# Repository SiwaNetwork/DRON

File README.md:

# 🚁 Final Drone Swarm Simulation

**Ультра-реалистичная симуляция роя дронов с многоуровневыми эшелонами, продвинутыми алгоритмами синхронизации и физически точными моделями связи**

## 🌟 Основные возможности

### ✈️ Многоуровневые эшелоны полета
- **5 эшелонов высоты** (60м - 140м)
- **Умное распределение дронов** по ролям
- **ПИД-регулятор высоты** для стабилизации
- **Автоматическое поддержание формации**

### 🔄 Продвинутая синхронизация
- **IEEE 1588 PTP** - точность до 10-100 наносекунд
- **NTP-подобные алгоритмы** для сетевой синхронизации
- **Консенсус-алгоритмы** для распределенной синхронизации
- **Адаптивная синхронизация** с компенсацией задержек

### 🕐 Различные типы генераторов тактовых импульсов
- **Мастер-дроны**: Rubidium, Cesium, GPS-Disciplined OCXO, Hydrogen Maser
- **Ведомые дроны**: OCXO, TCXO, Quartz, Crystal
- **Реалистичные характеристики** дрейфа и стабильности

### 🛡️ Система отказоустойчивости
- **Автоматическое переключение мастер-дрона**
- **Алгоритмы выборов лидера** (Priority, RAFT, Byzantine Fault Tolerant)
- **Обнаружение потери связи**
- **Восстановление синхронизации**

### 📡 Физически точные модели связи
- **Частотные диапазоны**: 433MHz, 900MHz, 1.2GHz, 2.4GHz, 5GHz, 5.8GHz
- **Ширина каналов**: 20/40/80/160 MHz
- **Модели помех**: Rural, Suburban, Urban, Indoor, Industrial
- **Уравнение Фрииса** для расчета затухания сигнала
- **Эффект Доплера** для движущихся дронов
- **Многолучевое распространение**
- **Атмосферное поглощение**

### 🎮 Интерактивная 3D визуализация
- **Three.js** для реалистичной графики
- **Реалистичные модели дронов** с вращающимися пропеллерами
- **Визуализация синхронизации** с цветными линиями
- **Реалистичная местность** с дорогами, зданиями, деревьями
- **Динамическое освещение** и туман

## 🚀 Быстрый старт

### Требования
- Python 3.7+
- Веб-браузер с поддержкой WebGL

### Установка и запуск
```bash
# Клонирование репозитория
git clone https://github.com/your-username/drone-swarm-simulation.git
cd drone-swarm-simulation

# Запуск симуляции
python final_drone_simulation.py
```

### Открытие в браузере
Автоматически откроется браузер по адресу: `http://localhost:8080`

## 🎯 Управление симуляцией

### Основные элементы интерфейса
1. **Панель конфигурации** (слева)
   - Параметры роя
   - Настройки синхронизации
   - Конфигурация отказоустойчивости
   - Радиочастотные параметры

2. **3D сцена** (центр)
   - Интерактивная камера (мышь)
   - Визуализация дронов и их движения
   - Линии синхронизации

3. **Панель метрик** (справа)
   - Время симуляции
   - Качество синхронизации
   - Статус DPLL
   - Информация об эшелонах

### Кнопки управления
- **Запустить симуляцию** - начало работы роя
- **Остановить симуляцию** - остановка всех процессов
- **Обновить конфигурацию** - применение новых параметров

## ⚙️ Конфигурация

### Параметры роя
- **Количество дронов**: 5-50
- **Радиус роя**: 100-2000 метров
- **Высота полета**: 50-300 метров

### Алгоритмы синхронизации
- **Master-Slave**: Классическая топология
- **Peer-to-Peer**: Равноправная синхронизация
- **Hierarchical**: Иерархическая структура
- **Mesh**: Сетевая топология

### Частотные диапазоны
- **433MHz**: Дальняя связь, низкая скорость
- **900MHz**: Средняя дальность
- **1.2GHz**: Авиационные частоты
- **2.4GHz**: WiFi диапазон
- **5GHz**: Высокоскоростная связь
- **5.8GHz**: FPV и управление

## 🔬 Технические детали

### Архитектура системы
```
┌─────────────────┐    ┌─────────────────┐    ┌─────────────────┐
│   Web Frontend  │    │  Python Backend │    │  Simulation     │
│   (Three.js)    │◄──►│  (HTTP Server)  │◄──►│  Engine         │
│                 │    │                 │    │                 │
│ - 3D Rendering  │    │ - API Endpoints │    │ - Drone Physics │
│ - UI Controls   │    │ - State Mgmt    │    │ - Sync Logic    │
│ - Real-time     │    │ - Threading     │    │ - Failover      │
└─────────────────┘    └─────────────────┘    └─────────────────┘
```

### Алгоритмы синхронизации

#### IEEE 1588 PTP (Precision Time Protocol)
```python
# Обмен сообщениями для точной синхронизации
Sync: Master → Slave (T1)
Follow_Up: Master → Slave (T1 точное время)
Delay_Req: Slave → Master (T2)
Delay_Resp: Master → Slave (T3)

# Расчет задержки и смещения
delay = ((T2 - T1) + (T4 - T3)) / 2
offset = ((T2 - T1) - (T4 - T3)) / 2
```

#### Консенсус-алгоритмы
- **RAFT**: Выбор лидера с логическими часами
- **Byzantine Fault Tolerant**: Защита от византийских ошибок
- **Priority-based**: Выбор по приоритету (тип часов, стабильность)

### Физические модели

#### Уравнение Фрииса
```
L = 20 * log10(f) + 20 * log10(d) + 20 * log10(4π/c) + L_extra
```
где:
- `f` - частота (Гц)
- `d` - расстояние (м)
- `c` - скорость света
- `L_extra` - дополнительные потери

#### Эффект Доплера
```
f_shift = f * (v * cos(θ)) / c
```
где:
- `f` - исходная частота
- `v` - относительная скорость
- `θ` - угол между векторами скорости и направления сигнала

## 📊 Метрики и мониторинг

### Качество синхронизации
- **Время смещения**: Разность времени между дронами
- **Джиттер**: Вариации задержки
- **Точность**: Стандартное отклонение ошибки
- **Стабильность**: Долгосрочная стабильность частоты

### Физические параметры
- **SNR**: Отношение сигнал/шум
- **Затухание сигнала**: Потери в канале связи
- **Многолучевые задержки**: Задержки от отражений
- **Доплеровский сдвиг**: Сдвиг частоты от движения

### Статус системы
- **Активный мастер**: Текущий ведущий дрон
- **Смены мастера**: Количество переключений
- **Активные выборы**: Текущие процессы выборов
- **Эшелоны**: Распределение по высотам

## 🎨 Визуализация

### Цветовая схема дронов
- **Красный**: Rubidium генераторы (мастер)
- **Зеленый**: OCXO генераторы
- **Синий**: TCXO генераторы
- **Желтый**: Quartz генераторы
- **Яркость**: Зависит от эшелона (темнее = ниже)

### Анимации
- **Вращение пропеллеров**: Реалистичное движение
- **Пульсация маяка**: Индикация мастер-дрона
- **Кольца синхронизации**: Визуализация качества связи
- **Линии связи**: Цветные линии между дронами

## 🔧 Расширение функциональности

### Добавление новых алгоритмов
```python
class CustomSyncAlgorithm:
    def __init__(self):
        self.name = "Custom Algorithm"
    
    def synchronize(self, drone, neighbors):
        # Ваша логика синхронизации
        pass
```

### Новые типы генераторов
```python
class CustomClock:
    def __init__(self):
        self.drift_rate = 1e-9  # дрейф в секундах/секунду
        self.stability = 1e-12  # стабильность Аллана
        self.accuracy = 1e-6    # точность в секундах
```

### Дополнительные модели помех
```python
def custom_interference_model(frequency, distance, environment):
    # Ваша модель помех
    return interference_level
```

## 📝 Лицензия

MIT License - см. файл [LICENSE](LICENSE)

## 🤝 Вклад в проект

1. Форкните репозиторий
2. Создайте ветку для новой функции
3. Внесите изменения
4. Создайте Pull Request

## 📞 Поддержка

- **Issues**: [GitHub Issues](https://github.com/your-username/drone-swarm-simulation/issues)
- **Discussions**: [GitHub Discussions](https://github.com/your-username/drone-swarm-simulation/discussions)
- **Email**: your-email@example.com

## 🙏 Благодарности

- **Three.js** - 3D графика
- **IEEE 1588** - стандарт точной синхронизации
- **DJI** - вдохновение для реалистичных параметров дронов

---

**Версия**: 2.0.0  
**Последнее обновление**: Август 2025  
**Автор**: Your Name

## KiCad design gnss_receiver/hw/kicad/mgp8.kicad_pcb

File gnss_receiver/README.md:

# МГП-8 — многосистемный многочастотный приёмник ГНСС (ШИВА.468157.001)

Открытая разработка модуля приёмника ГЛОНАСС/GPS/Galileo/BeiDou/QZSS/NavIC/SBAS.
В проект входят схема, конфигурация ПЛИС, программное обеспечение МК, моделирование
и конструкторская документация по ЕСКД.

Архитектура:

- 8 ВЧ-трактов MAX2771 (по схеме Pocket SDR FE 8CH), 2-битные I/Q, 24 МГц;
- ПЛИС LFE5U-45F (коррелятор на 80 каналов, режекторный фильтр, шкала времени, 1PPS);
- МК STM32H743 (захват, слежение, навигация, протоколы, шина FMC к ПЛИС);
- контроллер USB 3.0 FX3 для выдачи «сырых» отсчётов в формате Pocket SDR.

## Состав

| Каталог | Содержание |
|---|---|
| `docs/` | исходные тексты документов: обзор открытых разработок, ТЗ, ПЗ, ПМ, описание программы |
| `kd/` | КД в PDF (подлинник): Э1, Э3, ПЭ3, спецификация, ВП, ТЗ, ПЗ, ПМ, описание программы ПО МК; текстовые документы и перечни — также в DOCX (редактируемая копия для Word) |
| `hw/gen/` | схема Э3 «как код» (Python) → проект KiCad 7/10 (`hw/kicad/`), перечни ЕСКД |
| `hw/spice/` | SPICE-модели узлов: питание антенны, bias-tee, вход REF, выход 1PPS |
| `fpga/rtl/` | Verilog: `corr_engine` (16 каналов на движок), `corr_bank`, `notch`, `rf_capture`, `timebase`, `fmc_slave`, `max_spi`, `snapshot`, `acq_fft` (ускоритель захвата), `mgp8_core`, `mgp8_top` |
| `fpga/model/` | битово-точные модели коррелятора, режекторного фильтра и ускорителя захвата (Python) |
| `fpga/tb/` | тесты RTL: сверка с моделями, системный тест через шину FMC |
| `sw/fw/` | ПО МК (C99): драйвер коррелятора, захват (в т. ч. слабых сигналов), слежение (ФАП 3-го порядка, длительное накопление, повторный захват), GPS LNAV, строки ГЛОНАСС, Galileo I/NAV, BeiDou D1, эфемериды, PVT (GPS, ГЛОНАСС, Galileo, BeiDou), 1PPS, NMEA, RTCM 3.3, собственный двоичный протокол, спектральный контроль; тесты на ПК |
| `sw/pyrx/` | эталонный программный приёмник и имитатор сигналов (Python) |
| `sim/` | расчёты: частотный план, энергетика ВЧ-тракта, сигналы, PVT/DOP, режекторный фильтр, мощность и тепловой режим, надёжность |
| `tools/` | оформление PDF и DOCX по ЕСКД (рамки, штампы), шрифт osifont с исправлениями |

## Инструменты

Используются: Python 3 (numpy, scipy, matplotlib, reportlab, python-docx), Icarus Verilog,
Yosys, nextpnr-ecp5 и Project Trellis (ecppack), ngspice, gcc и KiCad 7 или 10 (kicad-cli).
Для `tests/check_output.py` нужны также pyrtcm и pynmeagps.

## Проверка

```sh
# ПЛИС: движок коррелятора, режекторный фильтр, система целиком (сверка с моделями)
make -C fpga sim
# ПЛИС: синтез, размещение и трассировка, файл конфигурации build/mgp8.bit
# (100,15 МГц при требуемых 96 МГц; готовый файл — fpga/bit/mgp8.bit)
make -C fpga syn
# ПО МК: модульные тесты (коды, модель ПЛИС, LNAV, строки ГЛОНАСС, I/NAV, D1, решение, протоколы,
# спектр и режекторный фильтр, захват слабых сигналов) и сквозной «ПЧ → слежение» (L1 C/A)
make -C sw/fw test
# ПО МК: длительные тесты (≈ 70 мин): динамика 4g, слабые сигналы и повторный захват,
# сквозные «ПЧ → координаты, 1PPS» по GPS, по GPS + ГЛОНАСС, двухчастотный GPS L1 + L2C,
# GPS + Galileo + BeiDou и двухчастотные пары L1 + L5, G1 + G2, E1 + E5a, B1I + B3I
make -C sw/fw test-long
# расчёты (результаты — sim/out/*.md, *.png)
python3 sim/rf_budget.py; python3 sim/freq_plan.py; python3 sim/notch_sim.py
python3 sim/power_budget.py; python3 sim/reliability.py
# схема и перечни (Э3, ПЭ3, спецификация, ВП); текстовые документы (ТЗ, ПЗ, ПМ, описание программы).
# Перечни и текстовые документы выходят в PDF и DOCX; правки вносятся в исходники (docs/*.md,
# hw/gen), DOCX пересобирается вместе с PDF
python3 hw/gen/build.py --pdf
python3 hw/gen/eskd_lists.py
python3 tools/build_docs.py
# вычислительное ядро ПО МК для STM32H743 (arm-none-eabi-gcc)
make -C sw/fw mcu
```

## Цепочка верификации

Каждый вычислительный блок ПЛИС описан дважды: битово-точной моделью на Python
и моделью на C (`sw/fw/src/corr_sim.c`), на которой работает ПО МК в тестах.
Результаты RTL сверяются с моделью отсчёт в отсчёт. Тесты ПО МК используют ту же
модель ПЛИС, поэтому сквозная проверка «ПЧ → координаты» проходит через реальные
регистры и протокол обмена ПЛИС–МК.

Выходные протоколы NMEA и RTCM дополнительно проверяются независимыми декодерами
(pynmeagps, pyrtcm).

## Копия на ПК

Рабочую копию репозитория в папке «Документы», обновляемую из GitHub по расписанию, ведут
скрипты `tools/sync/sync_documents.ps1` (Windows) и `tools/sync/sync_documents.sh`
(Linux, macOS). Установка — в `tools/sync/README.md`.

## Состояние

Результаты расчётов, моделирования и проверок, а также соответствие ТЗ сведены
в пояснительной записке (`docs/03_ПЗ.md`, `kd/ШИВА.468157.001 ПЗ.pdf`). Там же,
в разделе 9, перечислены нерешённые вопросы. Основные из них:

- разводка печатной платы;
- платформенная часть ПО МК;
- навигационное сообщение BeiDou D2 (КА GEO), пара BeiDou B1I + B2a (нужно сообщение B-CNAV);
- изготовление и испытания опытного образца.

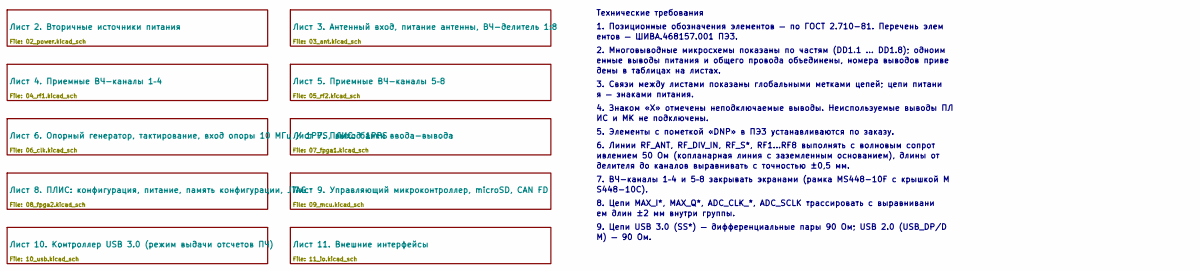
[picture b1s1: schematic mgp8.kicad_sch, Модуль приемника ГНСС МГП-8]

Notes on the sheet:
Технические требования
1. Позиционные обозначения элементов — по ГОСТ 2.710-81. Перечень элем
ентов — ШИВА.468157.001 ПЭ3.
2. Многовыводные микросхемы показаны по частям (DD1.1 … DD1.8); одноим
енные выводы питания и общего провода объединены, номера выводов приве
дены в таблицах на листах.
3. Связи между листами показаны глобальными метками цепей; цепи питани
я — знаками питания.
4. Знаком «X» отмечены неподключаемые выводы. Неиспользуемые выводы ПЛ
ИС и МК не подключены.
5. Элементы с пометкой «DNP» в ПЭ3 устанавливаются по заказу.
6. Линии RF_ANT, RF_DIV_IN, RF_S*, RF1…RF8 выполнять с волновым сопрот
ивлением 50 Ом (копланарная линия с заземленным основанием), длины от
делителя до каналов выравнивать с точностью ±0,5 мм.
7. ВЧ-каналы 1–4 и 5–8 закрывать экранами (рамка MS448-10F с крышкой M
S448-10C).
8. Цепи MAX_I*, MAX_Q*, ADC_CLK_*, ADC_SCLK трассировать с выравнивани
ем длин ±2 мм внутри группы.
9. Цепи USB 3.0 (SS*) — дифференциальные пары 90 Ом; USB 2.0 (USB_DP/D
M) — 90 Ом.

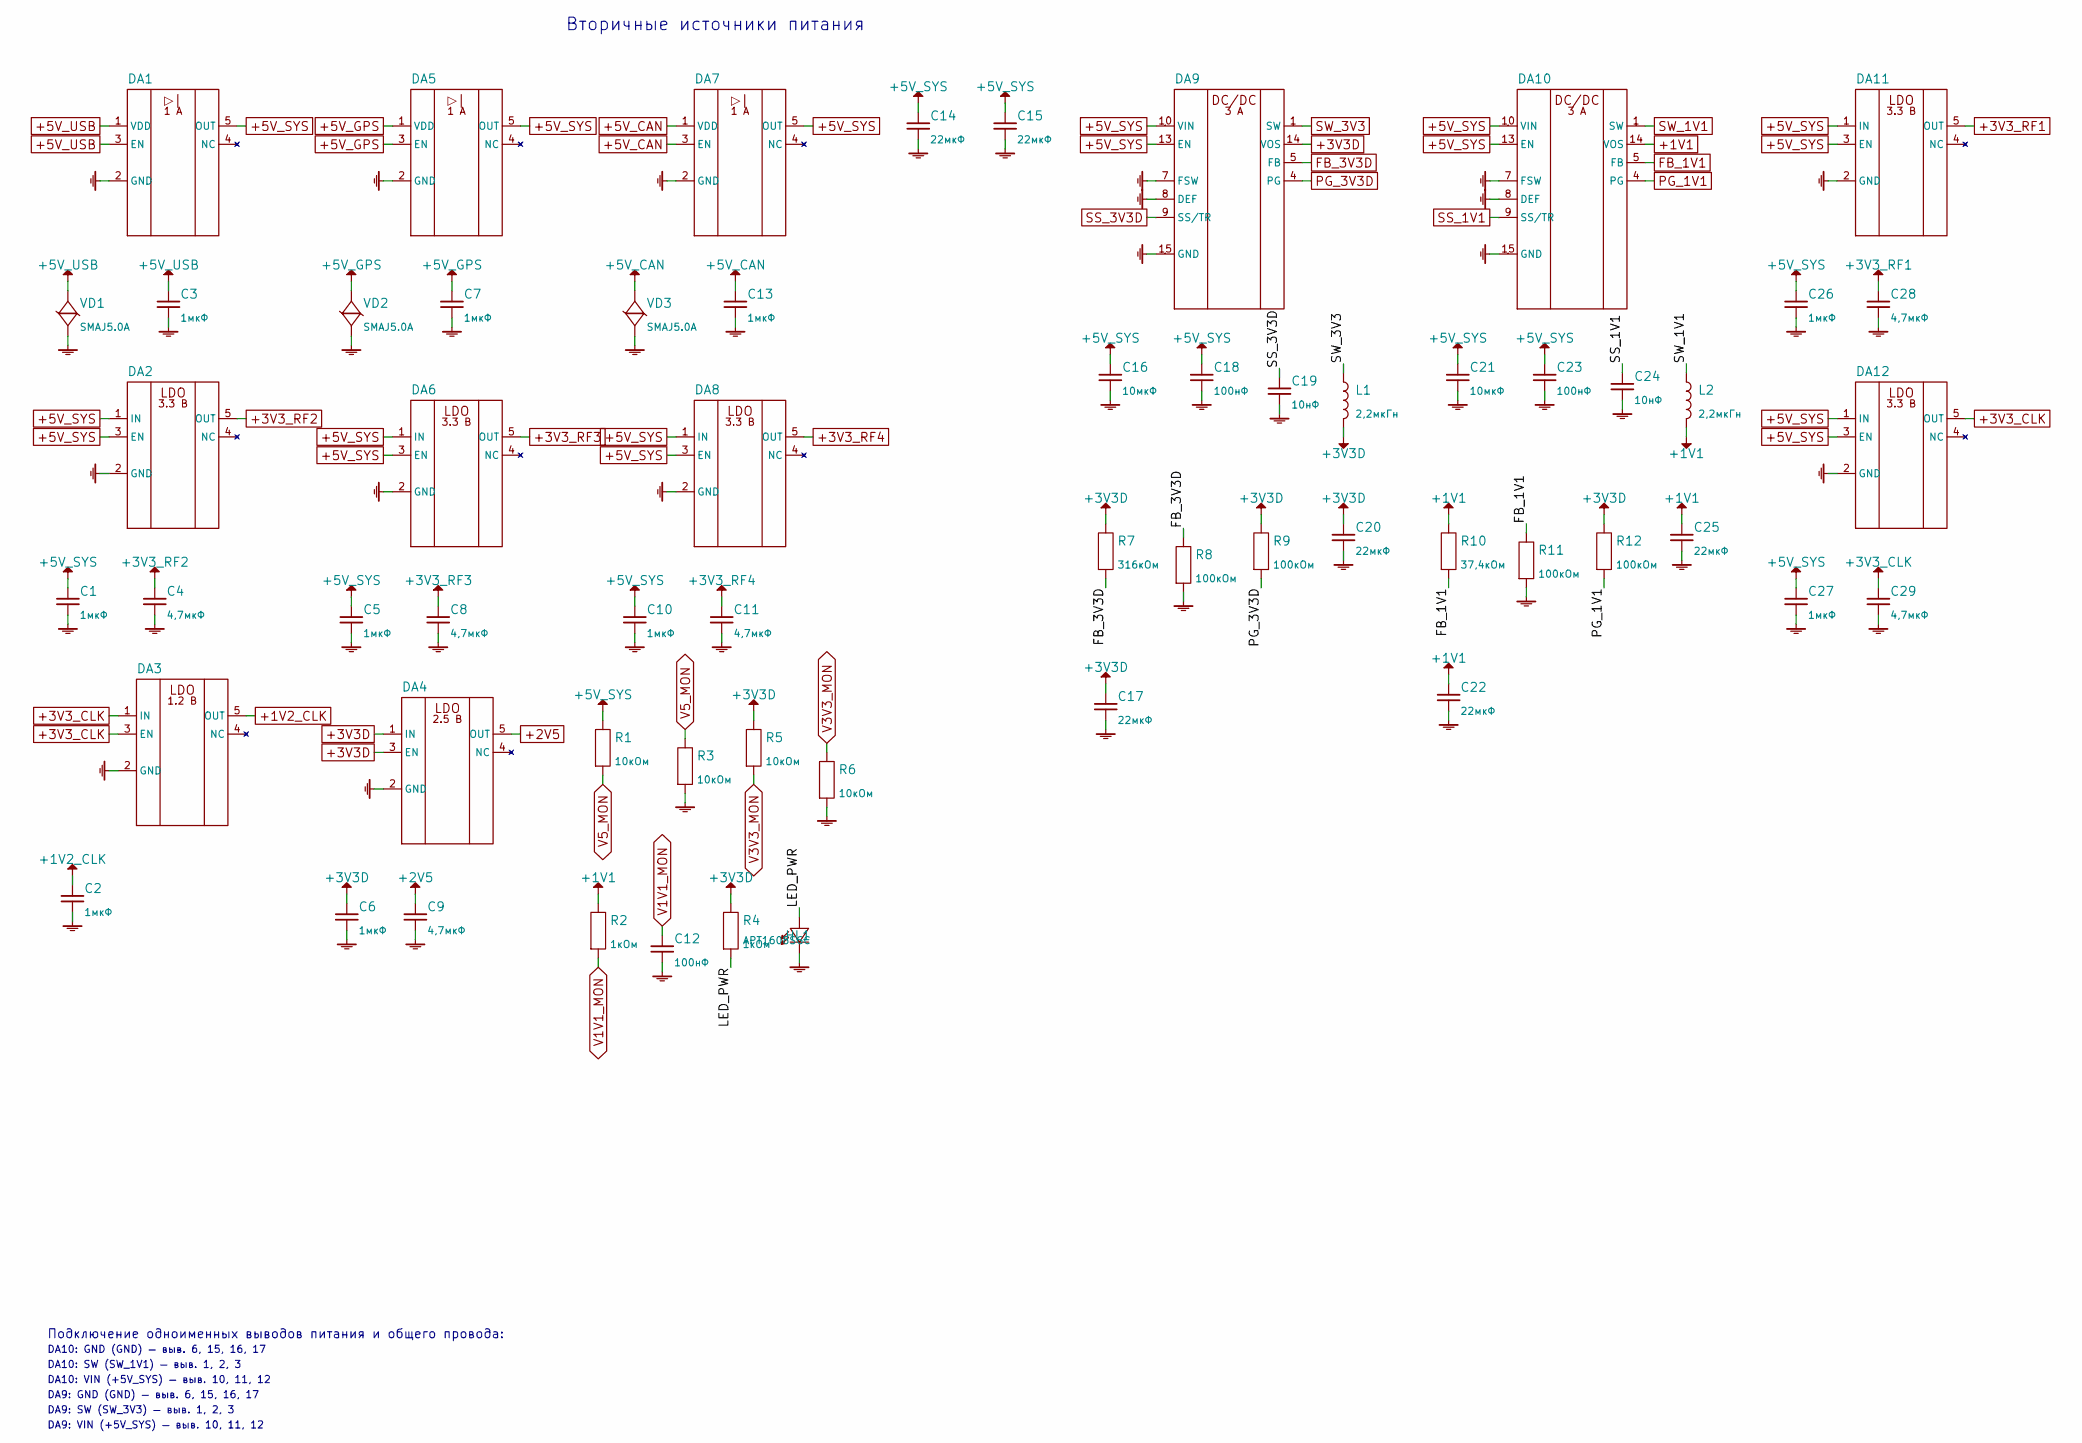
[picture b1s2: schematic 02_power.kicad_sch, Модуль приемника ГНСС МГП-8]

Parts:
C1, C2, C3, C5, C6, C7, C10, C13, C26, C27: 1мкФ; C_0402_1005Metric
C4, C8, C9, C11, C28, C29: 4,7мкФ; C_0402_1005Metric
C12, C18, C23: 100нФ; C_0402_1005Metric
C14, C15, C17, C20, C22, C25: 22мкФ; C_0603_1608Metric
C16, C21: 10мкФ; C_0603_1608Metric
C19, C24: 10нФ; C_0402_1005Metric
DA1, DA5, DA7: MAX40200AUK+T; SOT-23-5
DA2, DA6, DA8, DA11, DA12: LP5907MFX-3.3/NOPB; SOT-23-5
DA3: LP5907MFX-1.2/NOPB; SOT-23-5
DA4: LP5907MFX-2.5/NOPB; SOT-23-5
DA9, DA10: TPS62130RGTR; VQFN-16-1EP_3x3mm_P0.5mm_EP1.68x1.68mm_ThermalVias
HL1: APT1608SGC; LED_0603_1608Metric
L1, L2: 2,2мкГн; L_Coilcraft_XxL4020
R1, R3, R5, R6: 10кОм; R_0402_1005Metric
R2, R4: 1кОм; R_0402_1005Metric
R7: 316кОм; R_0402_1005Metric
R8, R9, R11, R12: 100кОм; R_0402_1005Metric
R10: 37,4кОм; R_0402_1005Metric
VD1, VD2, VD3: SMAJ5.0A; D_SMA

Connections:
+1V1: C22.1, C25.1, DA10.14 (VOS), L2.2, R2.1, R10.1; also elsewhere on the board
+1V2_CLK: C2.1, DA3.5 (OUT); also elsewhere on the board
+2V5: C9.1, DA4.5 (OUT); also elsewhere on the board
+3V3D: C6.1, C17.1, C20.1, DA4.1 (IN), DA4.3 (EN), DA9.14 (VOS), L1.2, R4.1, R5.1, R7.1, R9.1, R12.1; also elsewhere on the board
+3V3_CLK: C29.1, DA3.1 (IN), DA3.3 (EN), DA12.5 (OUT); also elsewhere on the board
+3V3_RF1: C28.1, DA11.5 (OUT); also elsewhere on the board
+3V3_RF2: C4.1, DA2.5 (OUT); also elsewhere on the board
+3V3_RF3: C8.1, DA6.5 (OUT); also elsewhere on the board
+3V3_RF4: C11.1, DA8.5 (OUT); also elsewhere on the board
+5V_CAN: C13.1, DA7.1 (VDD), DA7.3 (EN), VD3.1; also elsewhere on the board
+5V_GPS: C7.1, DA5.1 (VDD), DA5.3 (EN), VD2.1; also elsewhere on the board
+5V_SYS: C1.1, C5.1, C10.1, C14.1, C15.1, C16.1, C18.1, C21.1, C23.1, C26.1, C27.1, DA1.5 (OUT), DA2.1 (IN), DA2.3 (EN), DA5.5 (OUT), DA6.1 (IN), DA6.3 (EN), DA7.5 (OUT), DA8.1 (IN), DA8.3 (EN), DA9.10 (VIN), DA9.11, DA9.12, DA9.13 (EN), DA10.10 (VIN), DA10.11, DA10.12, DA10.13 (EN), DA11.1 (IN), DA11.3 (EN), DA12.1 (IN), DA12.3 (EN), R1.1; also elsewhere on the board
+5V_USB: C3.1, DA1.1 (VDD), DA1.3 (EN), VD1.1; also elsewhere on the board
/Лист 2. Вторичные источники питания/LED_PWR: HL1.2, R4.2
FB_1V1: DA10.5 (FB), R10.2, R11.1
FB_3V3D: DA9.5 (FB), R7.2, R8.1
GND: C1.2, C2.2, C3.2, C4.2, C5.2, C6.2, C7.2, C8.2, C9.2, C10.2, C11.2, C12.2, C13.2, C14.2, C15.2, C16.2, C17.2, C18.2, C19.2, C20.2, C21.2, C22.2, C23.2, C24.2, C25.2, C26.2, C27.2, C28.2, C29.2, DA1.2 (GND), DA2.2 (GND), DA3.2 (GND), DA4.2 (GND), DA5.2 (GND), DA6.2 (GND), DA7.2 (GND), DA8.2 (GND), DA9.6, DA9.7 (FSW), DA9.8 (DEF), DA9.15 (GND), DA9.16, DA9.17, DA10.6, DA10.7 (FSW), DA10.8 (DEF), DA10.15 (GND), DA10.16, DA10.17, DA11.2 (GND), DA12.2 (GND), HL1.1, R3.2, R6.2, R8.2, R11.2, VD1.2, VD2.2, VD3.2; also elsewhere on the board
PG_1V1: DA10.4 (PG), R12.2
PG_3V3D: DA9.4 (PG), R9.2
SS_1V1: C24.1, DA10.9 (SS/TR)
SS_3V3D: C19.1, DA9.9 (SS/TR)
SW_1V1: DA10.1 (SW), DA10.2, DA10.3, L2.1
SW_3V3: DA9.1 (SW), DA9.2, DA9.3, L1.1
V1V1_MON: C12.1, R2.2; also elsewhere on the board
V3V3_MON: R5.2, R6.1; also elsewhere on the board
V5_MON: R1.2, R3.1; also elsewhere on the board

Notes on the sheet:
Вторичные источники питания
Подключение одноименных выводов питания и общего провода:
DA10: GND (GND) — выв. 6, 15, 16, 17
DA10: SW (SW_1V1) — выв. 1, 2, 3
DA10: VIN (+5V_SYS) — выв. 10, 11, 12
DA9: GND (GND) — выв. 6, 15, 16, 17
DA9: SW (SW_3V3) — выв. 1, 2, 3
DA9: VIN (+5V_SYS) — выв. 10, 11, 12

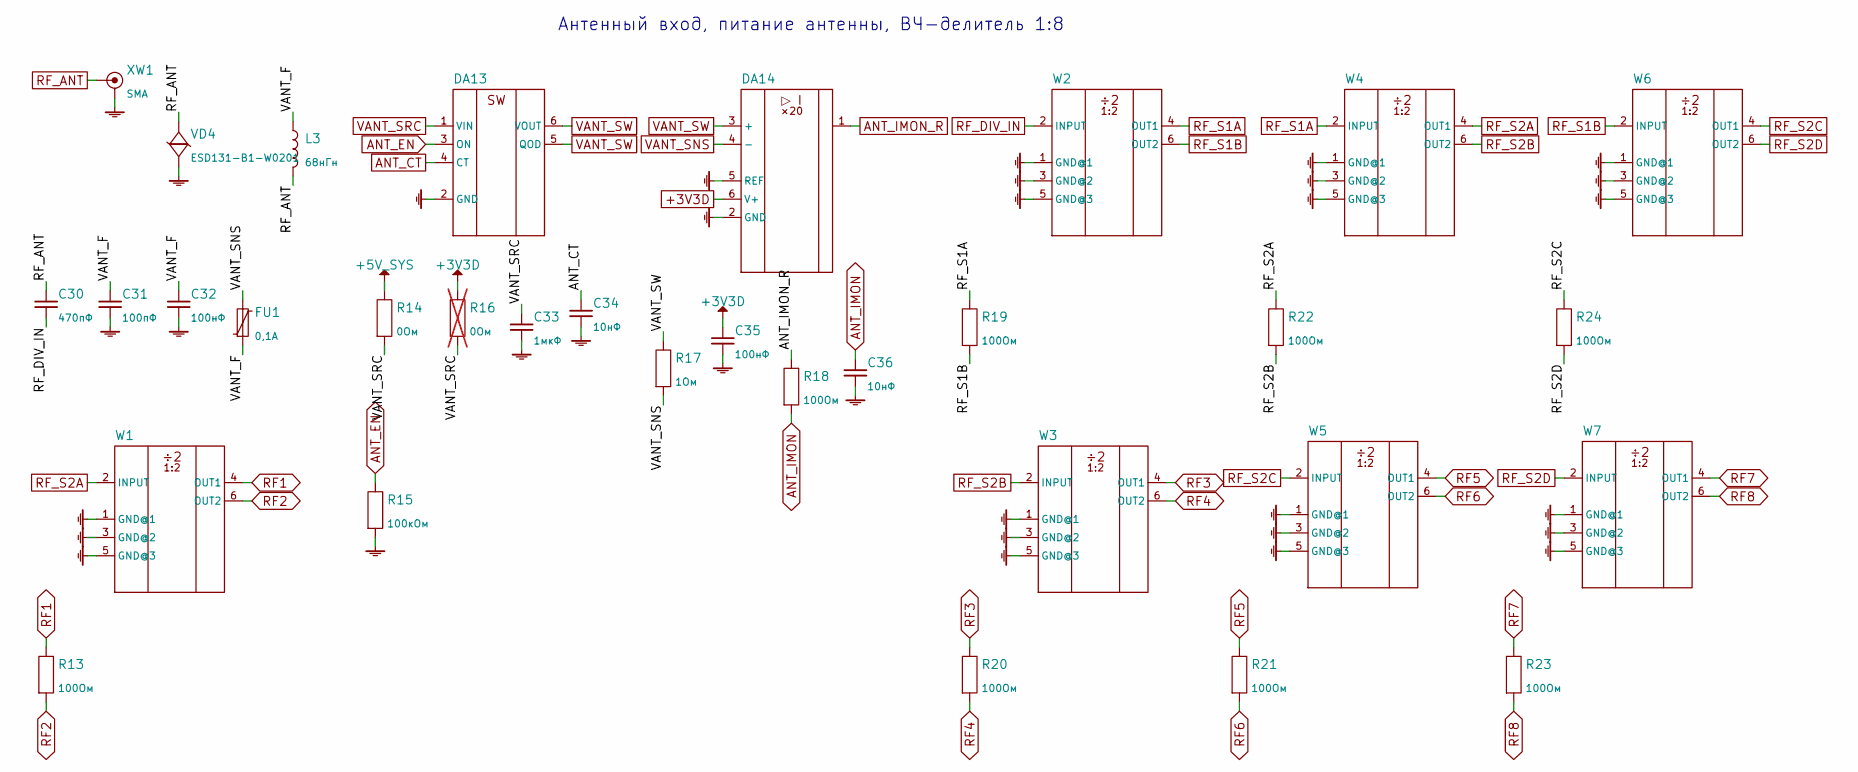
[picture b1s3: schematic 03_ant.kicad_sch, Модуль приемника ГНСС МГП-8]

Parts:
C30: 470пФ; C_0402_1005Metric
C31: 100пФ; C_0402_1005Metric
C32, C35: 100нФ; C_0402_1005Metric
C33: 1мкФ; C_0402_1005Metric
C34, C36: 10нФ; C_0402_1005Metric
DA13: TPS22917DBVR; SOT-23-6
DA14: INA181A1IDBVR; SOT-23-6
FU1: 0,1А; Fuse_0603_1608Metric
L3: 68нГн; L_0603_1608Metric
R13, R18, R19, R20, R21, R22, R23, R24: 100Ом; R_0402_1005Metric
R14: 0Ом; R_0402_1005Metric
R15: 100кОм; R_0402_1005Metric
R16: 0Ом; R_0402_1005Metric; not fitted
R17: 1Ом; R_0402_1005Metric
VD4: ESD131-B1-W0201; Infineon_SG-WLL-2-3_0.58x0.28_P0.36mm
W1, W2, W3, W4, W5, W6, W7: PD0922J5050S2HF; RF_DIV
XW1: SMA; SMA_Samtec_SMA-J-P-H-ST-EM1_EdgeMount

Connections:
+3V3D: C35.1, DA14.6 (V+), R16.1; also elsewhere on the board
+5V_SYS: R14.1; also elsewhere on the board
/Лист 3. Антенный вход, питание антенны, ВЧ-делитель 1:8/VANT_F: C31.1, C32.1, FU1.2, L3.1
ANT_CT: C34.1, DA13.4 (CT)
ANT_EN: DA13.3 (ON), R15.1; also elsewhere on the board
ANT_IMON: C36.1, R18.2; also elsewhere on the board
ANT_IMON_R: DA14.1, R18.1
GND: C31.2, C32.2, C33.2, C34.2, C35.2, C36.2, DA13.2 (GND), DA14.2 (GND), DA14.5 (REF), R15.2, VD4.2, W1.1 (GND@1), W1.3 (GND@2), W1.5 (GND@3), W2.1 (GND@1), W2.3 (GND@2), W2.5 (GND@3), W3.1 (GND@1), W3.3 (GND@2), W3.5 (GND@3), W4.1 (GND@1), W4.3 (GND@2), W4.5 (GND@3), W5.1 (GND@1), W5.3 (GND@2), W5.5 (GND@3), W6.1 (GND@1), W6.3 (GND@2), W6.5 (GND@3), W7.1 (GND@1), W7.3 (GND@2), W7.5 (GND@3), XW1.2; also elsewhere on the board
RF1: R13.1, W1.4 (OUT1); also elsewhere on the board
RF2: R13.2, W1.6 (OUT2); also elsewhere on the board
RF3: R20.1, W3.4 (OUT1); also elsewhere on the board
RF4: R20.2, W3.6 (OUT2); also elsewhere on the board
RF5: R21.1, W5.4 (OUT1); also elsewhere on the board
RF6: R21.2, W5.6 (OUT2); also elsewhere on the board
RF7: R23.1, W7.4 (OUT1); also elsewhere on the board
RF8: R23.2, W7.6 (OUT2); also elsewhere on the board
RF_ANT: C30.1, L3.2, VD4.1, XW1.1
RF_DIV_IN: C30.2, W2.2 (INPUT)
RF_S1A: R19.1, W2.4 (OUT1), W4.2 (INPUT)
RF_S1B: R19.2, W2.6 (OUT2), W6.2 (INPUT)
RF_S2A: R22.1, W1.2 (INPUT), W4.4 (OUT1)
RF_S2B: R22.2, W3.2 (INPUT), W4.6 (OUT2)
RF_S2C: R24.1, W5.2 (INPUT), W6.4 (OUT1)
RF_S2D: R24.2, W6.6 (OUT2), W7.2 (INPUT)
VANT_SNS: DA14.4 (-), FU1.1, R17.2
VANT_SRC: C33.1, DA13.1 (VIN), R14.2, R16.2
VANT_SW: DA13.5 (QOD), DA13.6 (VOUT), DA14.3 (+), R17.1

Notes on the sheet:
Антенный вход, питание антенны, ВЧ-делитель 1:8

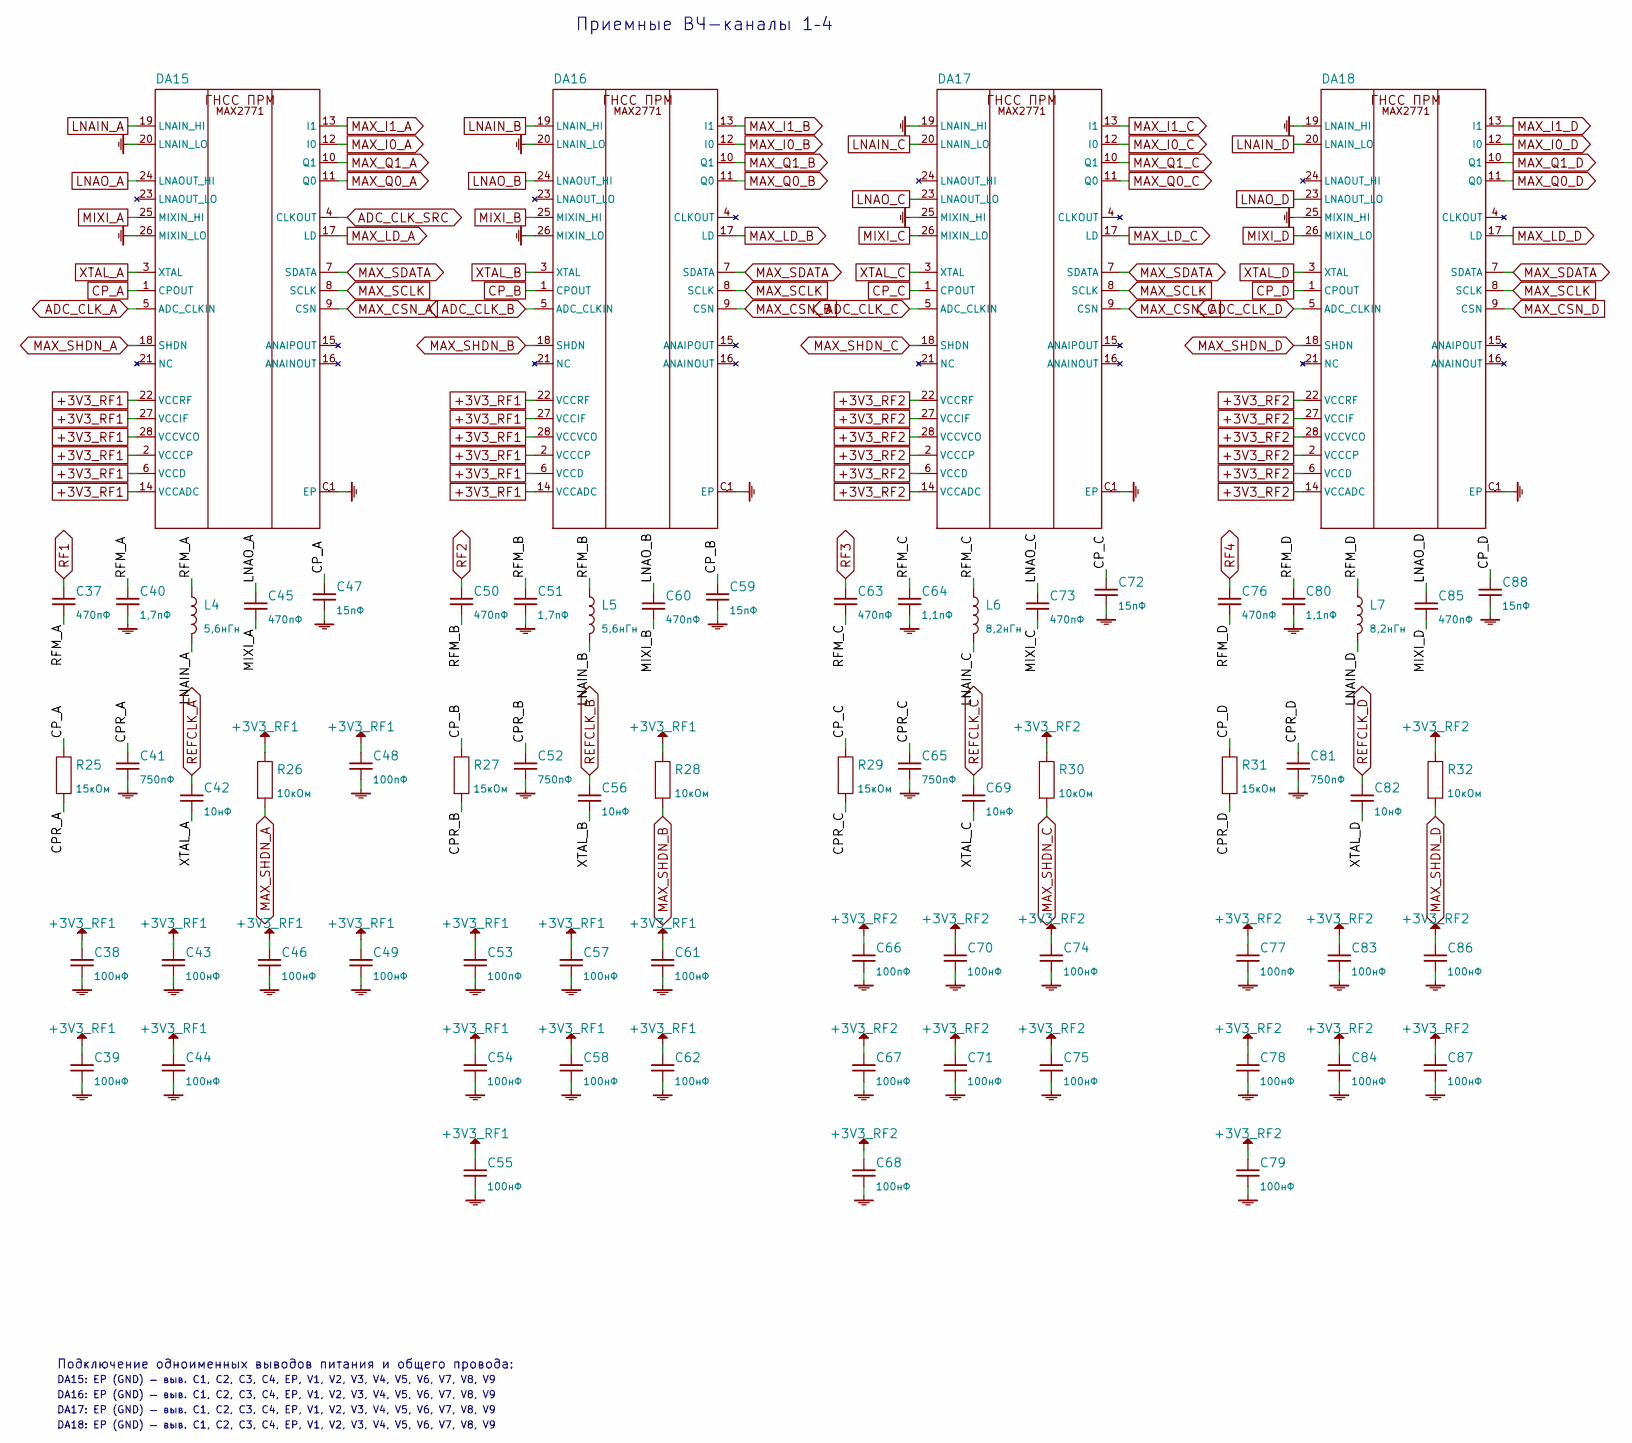
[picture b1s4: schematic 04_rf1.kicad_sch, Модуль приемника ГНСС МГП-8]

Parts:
C37, C45, C50, C60, C63, C73, C76, C85: 470пФ; C_0402_1005Metric
C38, C39, C43, C44, C46, C49, C54, C55, C57, C58, C61, C62, C67, C68, C70, C71, C74, C75, C78, C79, C83, C84, C86, C87: 100нФ; C_0402_1005Metric
C40, C51: 1,7пФ; C_0402_1005Metric
C41, C52, C65, C81: 750пФ; C_0402_1005Metric
C42, C56, C69, C82: 10нФ; C_0402_1005Metric
C47, C59, C72, C88: 15пФ; C_0402_1005Metric
C48, C53, C66, C77: 100пФ; C_0402_1005Metric
C64, C80: 1,1пФ; C_0402_1005Metric
DA15, DA16, DA17, DA18: MAX2771ETI+; TQFN28
L4, L5: 5,6нГн; L_0402_1005Metric
L6, L7: 8,2нГн; L_0402_1005Metric
R25, R27, R29, R31: 15кОм; R_0402_1005Metric
R26, R28, R30, R32: 10кОм; R_0402_1005Metric

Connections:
+3V3_RF1: C38.1, C39.1, C43.1, C44.1, C46.1, C48.1, C49.1, C53.1, C54.1, C55.1, C57.1, C58.1, C61.1, C62.1, DA15.2 (VCCCP), DA15.6 (VCCD), DA15.14 (VCCADC), DA15.22 (VCCRF), DA15.27 (VCCIF), DA15.28 (VCCVCO), DA16.2 (VCCCP), DA16.6 (VCCD), DA16.14 (VCCADC), DA16.22 (VCCRF), DA16.27 (VCCIF), DA16.28 (VCCVCO), R26.1, R28.1; also elsewhere on the board
+3V3_RF2: C66.1, C67.1, C68.1, C70.1, C71.1, C74.1, C75.1, C77.1, C78.1, C79.1, C83.1, C84.1, C86.1, C87.1, DA17.2 (VCCCP), DA17.6 (VCCD), DA17.14 (VCCADC), DA17.22 (VCCRF), DA17.27 (VCCIF), DA17.28 (VCCVCO), DA18.2 (VCCCP), DA18.6 (VCCD), DA18.14 (VCCADC), DA18.22 (VCCRF), DA18.27 (VCCIF), DA18.28 (VCCVCO), R30.1, R32.1; also elsewhere on the board
/Лист 4. Приемные ВЧ-каналы 1–4/CPR_A: C41.1, R25.2
/Лист 4. Приемные ВЧ-каналы 1–4/CPR_B: C52.1, R27.2
/Лист 4. Приемные ВЧ-каналы 1–4/CPR_C: C65.1, R29.2
/Лист 4. Приемные ВЧ-каналы 1–4/CPR_D: C81.1, R31.2
/Лист 4. Приемные ВЧ-каналы 1–4/RFM_A: C37.2, C40.1, L4.1
/Лист 4. Приемные ВЧ-каналы 1–4/RFM_B: C50.2, C51.1, L5.1
/Лист 4. Приемные ВЧ-каналы 1–4/RFM_C: C63.2, C64.1, L6.1
/Лист 4. Приемные ВЧ-каналы 1–4/RFM_D: C76.2, C80.1, L7.1
ADC_CLK_A: DA15.5 (ADC_CLKIN); also elsewhere on the board
ADC_CLK_B: DA16.5 (ADC_CLKIN); also elsewhere on the board
ADC_CLK_C: DA17.5 (ADC_CLKIN); also elsewhere on the board
ADC_CLK_D: DA18.5 (ADC_CLKIN); also elsewhere on the board
ADC_CLK_SRC: DA15.4 (CLKOUT); also elsewhere on the board
CP_A: C47.1, DA15.1 (CPOUT), R25.1
CP_B: C59.1, DA16.1 (CPOUT), R27.1
CP_C: C72.1, DA17.1 (CPOUT), R29.1
CP_D: C88.1, DA18.1 (CPOUT), R31.1
GND: C38.2, C39.2, C40.2, C41.2, C43.2, C44.2, C46.2, C47.2, C48.2, C49.2, C51.2, C52.2, C53.2, C54.2, C55.2, C57.2, C58.2, C59.2, C61.2, C62.2, C64.2, C65.2, C66.2, C67.2, C68.2, C70.2, C71.2, C72.2, C74.2, C75.2, C77.2, C78.2, C79.2, C80.2, C81.2, C83.2, C84.2, C86.2, C87.2, C88.2, DA15.20 (LNAIN_LO), DA15.26 (MIXIN_LO), DA15.C1 (EP), DA15.C2, DA15.C3, DA15.C4, DA15.EP, DA15.V1, DA15.V2, DA15.V3, DA15.V4, DA15.V5, DA15.V6, DA15.V7, DA15.V8, DA15.V9, DA16.20 (LNAIN_LO), DA16.26 (MIXIN_LO), DA16.C1 (EP), DA16.C2, DA16.C3, DA16.C4, DA16.EP, DA16.V1, DA16.V2, DA16.V3, DA16.V4, DA16.V5, DA16.V6, DA16.V7, DA16.V8, DA16.V9, DA17.19 (LNAIN_HI), DA17.25 (MIXIN_HI), DA17.C1 (EP), DA17.C2, DA17.C3, DA17.C4, DA17.EP, DA17.V1, DA17.V2, DA17.V3, DA17.V4, DA17.V5, DA17.V6, DA17.V7, DA17.V8, DA17.V9, DA18.19 (LNAIN_HI), DA18.25 (MIXIN_HI), DA18.C1 (EP), DA18.C2, DA18.C3, DA18.C4, DA18.EP, DA18.V1, DA18.V2, DA18.V3, DA18.V4, DA18.V5, DA18.V6, DA18.V7, DA18.V8, DA18.V9; also elsewhere on the board
LNAIN_A: DA15.19 (LNAIN_HI), L4.2
LNAIN_B: DA16.19 (LNAIN_HI), L5.2
LNAIN_C: DA17.20 (LNAIN_LO), L6.2
LNAIN_D: DA18.20 (LNAIN_LO), L7.2
LNAO_A: C45.1, DA15.24 (LNAOUT_HI)
LNAO_B: C60.1, DA16.24 (LNAOUT_HI)
LNAO_C: C73.1, DA17.23 (LNAOUT_LO)
LNAO_D: C85.1, DA18.23 (LNAOUT_LO)
MAX_CSN_A: DA15.9 (CSN); also elsewhere on the board
MAX_CSN_B: DA16.9 (CSN); also elsewhere on the board
MAX_CSN_C: DA17.9 (CSN); also elsewhere on the board
MAX_CSN_D: DA18.9 (CSN); also elsewhere on the board
MAX_I0_A: DA15.12 (I0); also elsewhere on the board
MAX_I0_B: DA16.12 (I0); also elsewhere on the board
MAX_I0_C: DA17.12 (I0); also elsewhere on the board
MAX_I0_D: DA18.12 (I0); also elsewhere on the board
MAX_I1_A: DA15.13 (I1); also elsewhere on the board
MAX_I1_B: DA16.13 (I1); also elsewhere on the board
MAX_I1_C: DA17.13 (I1); also elsewhere on the board
MAX_I1_D: DA18.13 (I1); also elsewhere on the board
MAX_LD_A: DA15.17 (LD); also elsewhere on the board
MAX_LD_B: DA16.17 (LD); also elsewhere on the board
MAX_LD_C: DA17.17 (LD); also elsewhere on the board
MAX_LD_D: DA18.17 (LD); also elsewhere on the board
MAX_Q0_A: DA15.11 (Q0); also elsewhere on the board
MAX_Q0_B: DA16.11 (Q0); also elsewhere on the board
MAX_Q0_C: DA17.11 (Q0); also elsewhere on the board
MAX_Q0_D: DA18.11 (Q0); also elsewhere on the board
MAX_Q1_A: DA15.10 (Q1); also elsewhere on the board
MAX_Q1_B: DA16.10 (Q1); also elsewhere on the board
MAX_Q1_C: DA17.10 (Q1); also elsewhere on the board
MAX_Q1_D: DA18.10 (Q1); also elsewhere on the board
MAX_SCLK: DA15.8 (SCLK), DA16.8 (SCLK), DA17.8 (SCLK), DA18.8 (SCLK); also elsewhere on the board
MAX_SDATA: DA15.7 (SDATA), DA16.7 (SDATA), DA17.7 (SDATA), DA18.7 (SDATA); also elsewhere on the board
MAX_SHDN_A: DA15.18 (SHDN), R26.2; also elsewhere on the board
MAX_SHDN_B: DA16.18 (SHDN), R28.2; also elsewhere on the board
MAX_SHDN_C: DA17.18 (SHDN), R30.2; also elsewhere on the board
MAX_SHDN_D: DA18.18 (SHDN), R32.2; also elsewhere on the board
MIXI_A: C45.2, DA15.25 (MIXIN_HI)
MIXI_B: C60.2, DA16.25 (MIXIN_HI)
MIXI_C: C73.2, DA17.26 (MIXIN_LO)
MIXI_D: C85.2, DA18.26 (MIXIN_LO)
REFCLK_A: C42.1; also elsewhere on the board
REFCLK_B: C56.1; also elsewhere on the board
REFCLK_C: C69.1; also elsewhere on the board
REFCLK_D: C82.1; also elsewhere on the board
RF1: C37.1; also elsewhere on the board
RF2: C50.1; also elsewhere on the board
RF3: C63.1; also elsewhere on the board
RF4: C76.1; also elsewhere on the board
XTAL_A: C42.2, DA15.3 (XTAL)
XTAL_B: C56.2, DA16.3 (XTAL)
XTAL_C: C69.2, DA17.3 (XTAL)
XTAL_D: C82.2, DA18.3 (XTAL)

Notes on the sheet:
Приемные ВЧ-каналы 1–4
Подключение одноименных выводов питания и общего провода:
DA15: EP (GND) — выв. C1, C2, C3, C4, EP, V1, V2, V3, V4, V5, V6, V7, V8, V9
DA16: EP (GND) — выв. C1, C2, C3, C4, EP, V1, V2, V3, V4, V5, V6, V7, V8, V9
DA17: EP (GND) — выв. C1, C2, C3, C4, EP, V1, V2, V3, V4, V5, V6, V7, V8, V9
DA18: EP (GND) — выв. C1, C2, C3, C4, EP, V1, V2, V3, V4, V5, V6, V7, V8, V9
